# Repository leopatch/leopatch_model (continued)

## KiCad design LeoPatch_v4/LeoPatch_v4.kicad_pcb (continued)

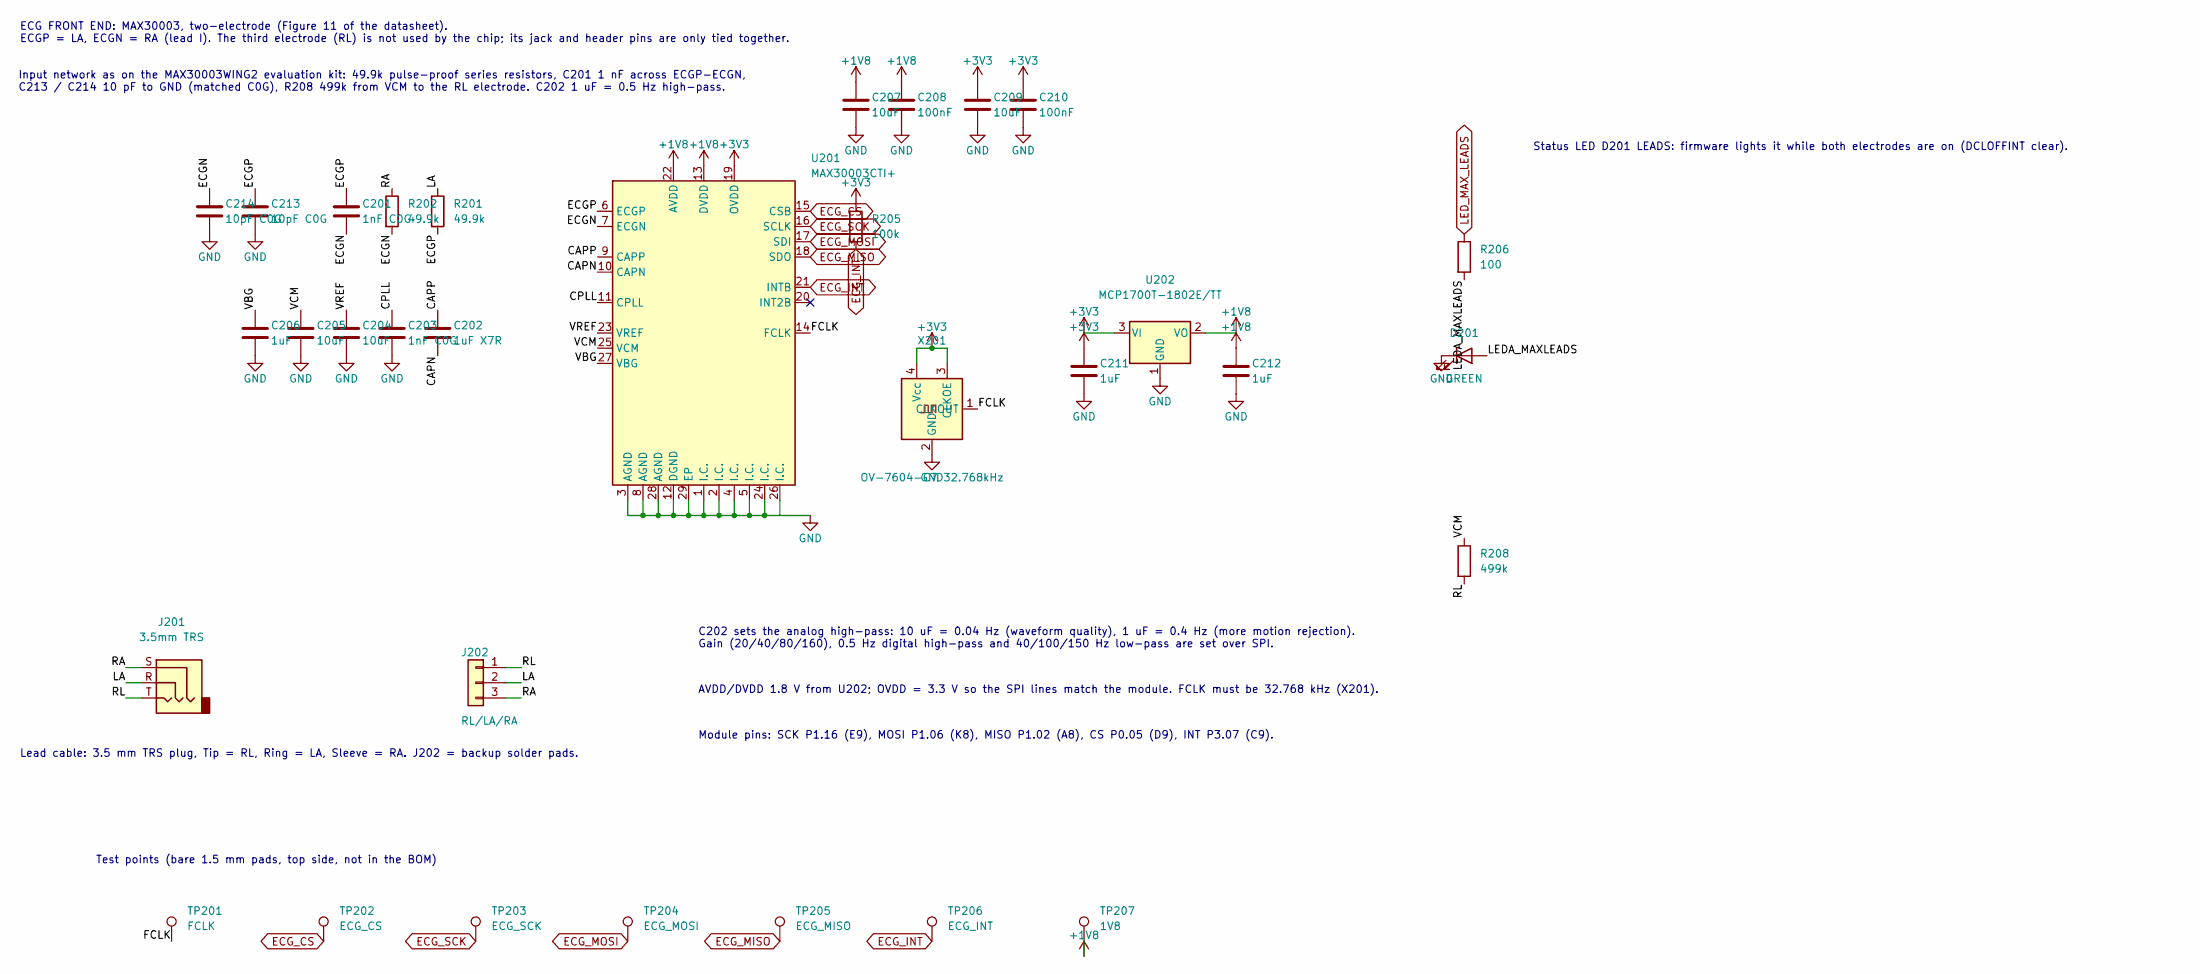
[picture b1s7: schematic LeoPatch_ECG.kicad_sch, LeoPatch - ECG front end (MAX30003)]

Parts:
C201, C203: 1nF C0G; C_0603_1608Metric; MPN CL10C102JB8NNNC; LCSC C163508
C202: 1uF X7R; C_0603_1608Metric; MPN CL10B105KP8NNNC; LCSC C95843
C204, C205, C207, C209: 10uF; C_0603_1608Metric; MPN CL10A106KP8NNNC; LCSC C19702
C206, C211, C212: 1uF; C_0603_1608Metric; MPN CL10A105KB8NNNC; LCSC C15849
C208, C210: 100nF; C_0603_1608Metric; MPN CC0603KRX7R9BB104; LCSC C14663
C213, C214: 10pF C0G; C_0603_1608Metric; MPN 0603CG100J500NT; LCSC C91367
D201: GREEN; LED_0603_1608Metric; MPN KT-0603G; LCSC C12624
J201: 3.5mm TRS; Jack_3.5mm_CUI_SJ-3523-SMT_Horizontal; MPN SJ-3523-SMT-TR; LCSC C4991872
J202: RL/LA/RA; PinHeader_1x03_P2.54mm_Vertical; MPN PZ254V-11-03P; LCSC C2937625
R201, R202: 49.9k; R_1206_3216Metric; MPN CRCW120649K9FKEAHP; LCSC C2089392
R205: 100k; R_0603_1608Metric; MPN 0603WAF1003T5E; LCSC C25803
R206: 100; R_0603_1608Metric; MPN 0603WAF1000T5E; LCSC C22775
R208: 499k; R_0603_1608Metric; MPN 0603WAF4993T5E; LCSC C26751
TP201: FCLK; TestPoint_Pad_D1.5mm
TP202: ECG_CS; TestPoint_Pad_D1.5mm
TP203: ECG_SCK; TestPoint_Pad_D1.5mm
TP204: ECG_MOSI; TestPoint_Pad_D1.5mm
TP205: ECG_MISO; TestPoint_Pad_D1.5mm
TP206: ECG_INT; TestPoint_Pad_D1.5mm
TP207: 1V8; TestPoint_Pad_D1.5mm
U201: MAX30003CTI+; TQFN-28-1EP_5x5mm_P0.5mm_EP3.25x3.25mm; MPN MAX30003CTI+T; LCSC C5354728
U202: MCP1700T-1802E/TT; SOT-23; MPN MCP1700T-1802E/TT; LCSC C150796
X201: OV-7604-C7 32.768kHz; Oscillator_SMD_SeikoEpson_SG3030CM; MPN OV-7604-C7-32.768kHz-20PPM-TA-QC; LCSC C5337982

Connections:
+1V8: C207.1, C208.1, C212.1, TP207.1, U201.13 (DVDD), U201.22 (AVDD), U202.2 (VO)
+3V3: C209.1, C210.1, C211.1, R205.1, U201.19 (OVDD), U202.3 (VI), X201.3 (CLKOE), X201.4 (Vcc); also elsewhere on the board
/ECG front end/CAPN: C202.2, U201.10 (CAPN)
/ECG front end/CAPP: C202.1, U201.9 (CAPP)
/ECG front end/CPLL: C203.1, U201.11 (CPLL)
/ECG front end/ECGN: C201.2, C214.1, R202.2, U201.7 (ECGN)
/ECG front end/ECGP: C201.1, C213.1, R201.2, U201.6 (ECGP)
/ECG front end/FCLK: TP201.1, U201.14 (FCLK), X201.1 (CLKOUT)
/ECG front end/LA: J201.R, J202.2, R201.1
/ECG front end/LEDA_MAXLEADS: D201.2 (A), R206.2
/ECG front end/RA: J201.S, J202.3, R202.1
/ECG front end/RL: J201.T, J202.1, R208.2
/ECG front end/VBG: C206.1, U201.27 (VBG)
/ECG front end/VCM: C205.1, R208.1, U201.25 (VCM)
/ECG front end/VREF: C204.1, U201.23 (VREF)
ECG_CS: TP202.1, U201.15 (CSB); also elsewhere on the board
ECG_INT: R205.2, TP206.1, U201.21 (INTB); also elsewhere on the board
ECG_MISO: TP205.1, U201.18 (SDO); also elsewhere on the board
ECG_MOSI: TP204.1, U201.17 (SDI); also elsewhere on the board
ECG_SCK: TP203.1, U201.16 (SCLK); also elsewhere on the board
GND: C203.2, C204.2, C205.2, C206.2, C207.2, C208.2, C209.2, C210.2, C211.2, C212.2, C213.2, C214.2, D201.1 (K), U201.1 (I.C.), U201.2 (I.C.), U201.3 (AGND), U201.4 (I.C.), U201.5 (I.C.), U201.8 (AGND), U201.12 (DGND), U201.24 (I.C.), U201.26 (I.C.), U201.28 (AGND), U201.29 (EP), U202.1 (GND), X201.2 (GND); also elsewhere on the board
LED_MAX_LEADS: R206.1; also elsewhere on the board

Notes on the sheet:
Lead cable: 3.5 mm TRS plug, Tip = RL, Ring = LA, Sleeve = RA. J202 = backup solder pads.
Input network as on the MAX30003WING2 evaluation kit: 49.9k pulse-proof series resistors, C201 1 nF across ECGP-ECGN, C213 / C214 10 pF to GND (matched C0G), R208 499k from VCM to the RL electrode. C202 1 uF = 0.5 Hz high-pass.
Status LED D201 LEADS: firmware lights it while both electrodes are on (DCLOFFINT clear).
ECG FRONT END: MAX30003, two-electrode (Figure 11 of the datasheet). ECGP = LA, ECGN = RA (lead I). The third electrode (RL) is not used by the chip; its jack and header pins are only tied together.
Test points (bare 1.5 mm pads, top side, not in the BOM)
Module pins: SCK P1.16 (E9), MOSI P1.06 (K8), MISO P1.02 (A8), CS P0.05 (D9), INT P3.07 (C9).
C202 sets the analog high-pass: 10 uF = 0.04 Hz (waveform quality), 1 uF = 0.4 Hz (more motion rejection). Gain (20/40/80/160), 0.5 Hz digital high-pass and 40/100/150 Hz low-pass are set over SPI.
AVDD/DVDD 1.8 V from U202; OVDD = 3.3 V so the SPI lines match the module. FCLK must be 32.768 kHz (X201).

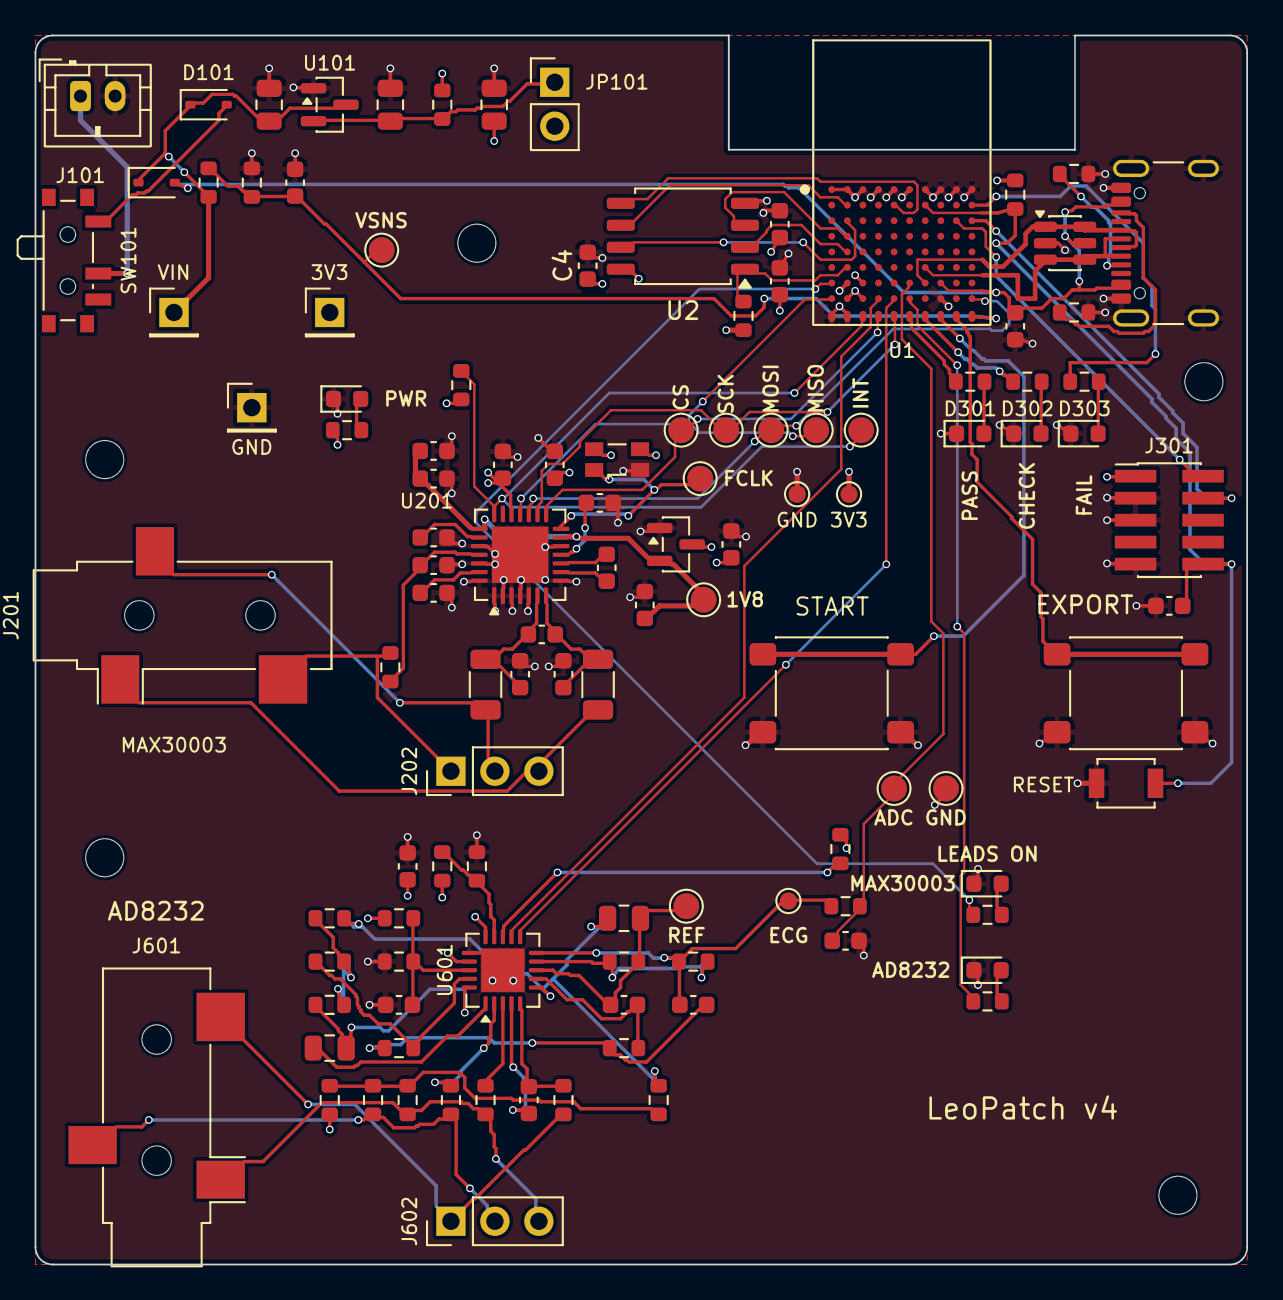
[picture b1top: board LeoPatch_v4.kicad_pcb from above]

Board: 4 copper layers, 70.0 x 71.0 mm, 118 parts (0 on the bottom side), 76 nets.

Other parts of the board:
H1, H2, H3, H4, H5: M2; MountingHole_2.2mm_M2

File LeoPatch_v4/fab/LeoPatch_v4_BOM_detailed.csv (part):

"Designator","Qty","Manufacturer","MPN","LCSC","Description","Footprint","Mount","Datasheet","Note"
"C1,C105","2","Samsung Electro-Mechanics","CL10A475KO8NNNC","C19666","4.7uF 16V X5R 10% 0603 MLCC","C_0603_1608Metric","SMD","https://www.lcsc.com/datasheet/lcsc_datasheet_2304140030_Sam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","JLC basic"
"C2,C3,C4,C104,C208,C210,C605,C607","8","YAGEO","CC0603KRX7R9BB104","C14663","100nF 50V X7R 10% 0603 MLCC","C_0603_1608Metric","SMD","https://www.lcsc.com/datasheet/lcsc_datasheet_2211101700_YAG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","JLC basic"
"C101,C102,C103","3","Samsung Electro-Mechanics","CL21A106KAYNNNE","C15850","10uF 25V X5R 10% 0805 MLCC","C_0805_2012Metric","SMD","https://www.lcsc.com/datasheet/lcsc_datasheet_2304140030_Sam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","JLC basic (C101 was 16V and C102/C103 10V in the schematic; 25V covers all three)"
"C201,C203,C601,C602","4","Samsung Electro-Mechanics","CL10C102JB8NNNC","C163508","1nF 50V C0G/NP0 5% 0603 MLCC","C_0603_1608Metric","SMD","https://www.lcsc.com/datasheet/lcsc_datasheet_2304140030_Sam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","C0G: MAX30003 ECGP-ECGN differential cap (eval kit C10 1nF), PLL, AD8232 filter"
"C202","1","Samsung Electro-Mechanics","CL10B105KP8NNNC","C95843","1uF 10V X7R 10% 0603 MLCC","C_0603_1608Metric","SMD","https://www.lcsc.com/datasheet/lcsc_datasheet_2304140030_Sam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","MAX30003 CAPP-CAPN, 0.5 Hz analog high-pass (datasheet default, eval kit C9); settles in ~1-2 s"
"C204,C205,C207,C209","4","Samsung Electro-Mechanics","CL10A106KP8NNNC","C19702","10uF 10V X5R 10% 0603 MLCC","C_0603_1608Metric","SMD","https://www.lcsc.com/datasheet/lcsc_datasheet_2304140030_Sam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","JLC basic"
"C206,C211,C212","3","Samsung Electro-Mechanics","CL10A105KB8NNNC","C15849","1uF 50V X5R 10% 0603 MLCC","C_0603_1608Metric","SMD","https://www.lcsc.com/datasheet/lcsc_datasheet_2304140030_Sam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","JLC basic"
"C603","1","FH (Guangdong Fenghua)","0603CG122J500NT","C68659","1.2nF 50V C0G/NP0 5% 0603 MLCC","C_0603_1608Metric","SMD","https://wmsc.lcsc.com/wmsc/upload/file/pdf/v2/lcsc/230414003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","AD8232 low-pass (C0G)"
"C604,C606","2","YAGEO","CC0805KKX7R9BB334","C107132","330nF 50V X7R 10% 0805 MLCC","C_0805_2012Metric","SMD","https://www.lcsc.com/datasheet/lcsc_datasheet_2304140030_YAG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","AD8232 high-pass"
"D101,D102","2","STMicroelectronics","BAT54JFILM","C86299","Schottky diode 40V 300mA SOD-323","D_SOD-323","SMD","https://www.lcsc.com/datasheet/lcsc_datasheet_2304140030_STM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","fits the SOD-323 footprint"
"D103,D201,D301,D601","4","Hubei KENTO","KT-0603G","C12624","LED green 525nm 0603","LED_0603_1608Metric","SMD","https://www.lcsc.com/datasheet/lcsc_datasheet_1806151818_Hub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","PASS, PWR, MAX30003 LEADS, AD8232 LEADS"
"D302","1","Hubei KENTO","KT-0603Y","C2287","LED yellow 590nm 0603","LED_0603_1608Metric","SMD","https://www.lcsc.com/product-detail/led-indication-discrete_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","CHECK"
"D303","1","Hubei KENTO","KT-0603R","C2286","LED red 625nm 0603","LED_0603_1608Metric","SMD","https://www.lcsc.com/datasheet/lcsc_datasheet_1810231112_Hub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","FAIL - JLC basic"
"J101","1","JST","B2B-PH-K-S(LF)(SN)","C131337","JST PH 2-pin header vertical 2.0mm, through-hole","JST_PH_B2B-PH-K_1x02_P2.00mm_Vertical","through-hole","https://www.lcsc.com/datasheet/lcsc_datasheet_2304140030_JST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","battery lead connector (mates PHR-2); through-hole"
"J102","1","Global Connector Technology","USB4105-GF-A","C3020560","USB Type-C receptacle USB 2.0 16P SMD right-angle","USB_C_Receptacle_GCT_USB4105-xx-A_16P_TopMnt_Horizontal","SMD","https://wmsc.lcsc.com/wmsc/upload/file/pdf/v2/lcsc/230414003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",""
"J103,J104,J105","3","XFCN","PZ254V-11-01P","C492400","Pin header 1x1 2.54mm vertical, through-hole","PinHeader_1x01_P2.54mm_Vertical","through-hole","https://www.lcsc.com/datasheet/lcsc_datasheet_2003141409_XFC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","alligator-clip pins; through-hole"
"J201,J601","2","CUI Devices","SJ-3523-SMT-TR","C4991872","3.5mm stereo (TRS) audio jack SMD right-angle","Jack_3.5mm_CUI_SJ-3523-SMT_Horizontal","SMD","https://wmsc.lcsc.com/wmsc/upload/file/pdf/v2/lcsc/240126111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","JLC Global Sourcing (DigiKey CP-3523SJCT-ND)"
"J202,J602","2","XFCN","PZ254V-11-03P","C2937625","Pin header 1x3 2.54mm vertical, through-hole","PinHeader_1x03_P2.54mm_Vertical","through-hole","https://wmsc.lcsc.com/wmsc/upload/file/pdf/v2/lcsc/220112180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","electrode backup header; through-hole"
"J301","1","hanxia","HX PZ1.27-2x5P TP","C41376037","Pin header 2x5 1.27mm SMD vertical (ARM SWD 10-pin)","PinHeader_2x05_P1.27mm_Vertical_SMD","SMD","https://www.lcsc.com/datasheet/lcsc_datasheet_2408301019_han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","SWD programming header"
"JP101","1","XFCN","PZ254V-11-02P","C492401","Pin header 1x2 2.54mm vertical, through-hole","PinHeader_1x02_P2.54mm_Vertical","through-hole","https://www.lcsc.com/datasheet/lcsc_datasheet_2409302300_XFC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","current-measure jumper; needs a 2.54 mm jumper cap (not assembled)"
"R1,R615","2","UNI-ROYAL","0603WAF1002T5E","C25804","10k 1% 100mW 0603 thick film","R_0603_1608Metric","SMD","https://www.lcsc.com/datasheet/lcsc_datasheet_2206010045_UNI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","JLC basic"
"R2,R205","2","UNI-ROYAL","0603WAF1003T5E","C25803","100k 1% 100mW 0603 thick film","R_0603_1608Metric","SMD","https://www.lcsc.com/datasheet/lcsc_datasheet_2206010045_UNI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","JLC basic"
"R101,R617,R619","3","UNI-ROYAL","0603WAF0000T5E","C21189","0R jumper 0603","R_0603_1608Metric","SMD","https://www.lcsc.com/datasheet/lcsc_datasheet_2411221126_UNI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","JLC basic"
"R102,R606,R607,R608,R609","5","UNI-ROYAL","0603WAF1004T5E","C22935","1M 1% 100mW 0603 thick film","R_0603_1608Metric","SMD","https://www.lcsc.com/datasheet/lcsc_datasheet_2206010130_UNI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","JLC basic"
"R103","1","UNI-ROYAL","0603WAF3303T5E","C23137","330k 1% 100mW 0603 thick film","R_0603_1608Metric","SMD","https://www.lcsc.com/datasheet/lcsc_datasheet_2206010116_UNI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","JLC basic"
"R104,R105","2","UNI-ROYAL","0603WAF5101T5E","C23186","5.1k 1% 100mW 0603 thick film","R_0603_1608Metric","SMD","https://www.lcsc.com/datasheet/lcsc_datasheet_2206010116_UNI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","USB-C CC pull-downs - JLC basic"
"R106,R302,R303,R623","4","UNI-ROYAL","0603WAF1001T5E","C21190","1k 1% 100mW 0603 thick film","R_0603_1608Metric","SMD","https://www.lcsc.com/datasheet/lcsc_datasheet_2206010130_UNI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","1k: LED resistors (yellow/red/power), AD8232 output RC (R623)"
"R201,R202","2","Vishay","CRCW120649K9FKEAHP","C2089392","49.9k 1% 750mW 1206 pulse-proof thick film","R_1206_3216Metric","SMD","https://wmsc.lcsc.com/wmsc/upload/file/pdf/v2/lcsc/230414003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","MAX30003 electrode series resistors (MAX30003WING2 eval kit: 49.9k R4/R5); pulse-proof for ESD"
"R206,R301,R621","3","UNI-ROYAL","0603WAF1000T5E","C22775","100R 1% 100mW 0603 thick film","R_0603_1608Metric","SMD","https://www.lcsc.com/datasheet/lcsc_datasheet_2411221126_UNI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","100R: green LED resistors (InGaN green needs ~3 V)"
"R601,R602,R610,R611,R613,R614","6","UNI-ROYAL","0603WAF1005T5E","C7250","10M 1% 100mW 0603 thick film","R_0603_1608Metric","SMD","https://www.lcsc.com/datasheet/lcsc_datasheet_2206010216_UNI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","JLC basic"
"R603,R604,R605","3","UNI-ROYAL","0603WAF3603T5E","C23146","360k 1% 100mW 0603 thick film","R_0603_1608Metric","SMD","https://www.lcsc.com/datasheet/lcsc_datasheet_2206010116_UNI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","AD8232 electrode + RLD safety resistors: >= 3.3 V / 10 uA = 330k (AD8232 datasheet p21, p26)"
"R612","1","UNI-ROYAL","0603WAF1404T5E","C38070","1.4M 1% 100mW 0603 thick film","R_0603_1608Metric","SMD","https://www.lcsc.com/datasheet/lcsc_datasheet_2206010000_UNI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",""
"SW101","1","C&K","PCM12SMTR","C221841","Slide switch SPDT SMD right-angle","SW_SPDT_PCM12","SMD","https://www.lcsc.com/datasheet/lcsc_datasheet_1912111437_C-K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","power on/off"
"SW301,SW302","2","C&K","PTS645SM43SMTR92 LFS","C221880","Tactile switch 6x6mm SMD 4.3mm 160gf","SW_SPST_PTS645Sx43SMTR92","SMD","https://www.lcsc.com/datasheet/lcsc_datasheet_2410121928_C-K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","EXPORT / START"
"SW303","1","Omron","B3U-1000P","C231329","Tactile switch 3x2.5mm SMD","SW_SPST_B3U-1000P","SMD","https://www.lcsc.com/product-detail/tactile-switches_omron-e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","RESET"
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
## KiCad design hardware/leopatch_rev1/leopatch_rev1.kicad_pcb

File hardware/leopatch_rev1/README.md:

# LeoPatch Rev 1 (KiCad 9)

The bare-minimum board for LeoPatch: the nRF54LM20 DK (PCA10184 v0.7.0) reduced to the parts the patch
needs, plus an AD8232 ECG front end, a LiPo battery and a 2.7 V supply. The reasoning is in
[../LeoPatch_Rev1_PCB_Plan.pdf](../LeoPatch_Rev1_PCB_Plan.pdf).

## What's on the board

| Block | Parts |
|---|---|
| Radio core (copied from the DK) | U1 nRF54LM20B, crystals X1/X2, DC/DC and decoupling, antenna tuning, test connector J1, PCB antenna |
| Power | U3 nPM1300 charger and 2.7 V supply, J10 LiPo connector, RT1 battery thermistor |
| USB-C | J3 with ESD protection D1 and choke L8 (charging and USB data) |
| Storage | U4 8 MB flash |
| User interface | LD1–LD3 green/amber/red status LEDs, SW1 record/upload button |
| Programming | P11 SWD header (connect to the DK's Debug OUT) |
| ECG | U20 AD8232 (datasheet Fig. 66), J11 electrode connector: 1 LA, 2 RA, 3 RL |
| Bring-up test points | VBAT, VSYS, VDD_NRF, ECG_OUT, GND, UART TX/RX |

Removed from the DK:
- the debugger and its USB port
- the switches and level shifters
- all pin headers
- the NFC connector
- the extra LEDs and buttons
- the reset button (the SWD header can reset the chip)
- the DK's test points

## Files

| File | What it is |
|---|---|
| `leopatch_rev1.kicad_pro` | Open this in KiCad |
| `leopatch_rev1.kicad_sch` + 5 sheets | Root sheet, plus `radio`, `power`, `usb`, `io` and `ecg` sheets |
| `leopatch_rev1.kicad_pcb` | The board, already updated to match the schematic |
| `libraries/leopatch.kicad_sym` | Symbols: nRF54LM20B, nPM1300, AD8232, MX25R6435F, USB-C, ESD, choke, RF connector, MOSFET |
| `libraries/leopatch_dk.pretty` | The DK's own footprints, copied from its board |
| `libraries/leopatch.pretty` | AD8232 LFCSP-20 (CP-20-10) and JST PH connectors |
| `reference/` | The unmodified DK board converted to KiCad, for comparison |

The libraries are registered in this folder's `sym-lib-table` and `fp-lib-table`, so the project opens
the same on any Mac with KiCad 9.

## What has been checked

- **Schematic vs. design:** every pin (412) connects to the intended net, checked against KiCad's
  exported netlist.
- **Electrical rules check:** 0 errors, 0 warnings.
- **Schematic vs. PCB** (KiCad's schematic parity check): 0 differences. Every part is on the board,
  with the right footprint, value and nets.
- **Routing:** kept parts keep the DK's routing between them. Routing that only went to removed parts
  was deleted.
- **Design rules:** set to the smallest features Nordic's layout uses. Those are 0.1 mm clearance,
  0.2 mm microvias with 0.1 mm drills, and 0.05 mm annular rings, and the DK's 8-layer filled-via
  stack-up supports them.

## Next steps in the PCB Editor

1. **Place the new parts** sitting below the board: J11 (electrodes), J10 (battery), U20 and its
   R2xx/C2xx parts, RT1, C101, R101/R102 and the test points. Put the ECG section far from the antenna
   (right edge) and from the nPM1300's inductors L6/L7.
2. **Route the 110 unrouted connections.** The ratsnest lines show them. Most are the new parts. The
   rest are connections that went through removed DK parts:
   - flash U4 straight to P2.00–P2.05
   - crystal X2 to XL1/XL2
   - nPM1300 I2C (SDA P1.12, SCL P1.13), GPIO1 and GPIO3 to the nRF54
   - USB CC1/CC2 and VBUS to the nPM1300
3. **Shrink the board outline** if you like. Keep the antenna corner, its copper-free area and the
   ground around it as they are.
4. **Leave the radio section alone:** U1 and its capacitors, X1, X2, L1, L5, FB1, FB2, C6–C8, C14,
   L2–L4, C3, C12, C13, J1, C76 and the antenna copper.
5. **Run the DRC.** Items that came with the DK file itself:
   - 3 tiny Edge.Cuts segments (they go away when you redraw the outline)
   - USB vias inside a keepout
   - the USB shield copper
   - "footprint doesn't match library" warnings, which are cosmetic

After editing the schematic, use **Tools → Update PCB from Schematic** as normal. Footprints are already
linked to their symbols.

## Design notes

- **2.7 V supply:** R17 = 330 kΩ sets the nPM1300's VOUT1 start-up voltage (250–500 kΩ = 2.7 V). The
  AD8232 needs at least 2.0 V.
- **ECG filter:** C204 = 10 nF and C205 = 1.5 nF give the datasheet's 40 Hz low-pass. 3.3 nF and
  470 pF move it to about 128 Hz, closer to the model's training data. Try both.
- **Pin map:**
  - LED0, LED1, LED2 on P1.22, P1.25, P1.27; button on P1.26
  - flash on P2.00–P2.05
  - ECG OUT on P1.03/AIN7; SDN, LO+, LO− on P1.11, P1.14, P1.15
  - PMIC SDA, SCL on P1.12, P1.13; LED power on P1.10; PMIC interrupt on P1.24. I2C clocks must use
    the chip's clock pins (datasheet table 79); P1's clock pins are P1.03, P1.04, P1.07, P1.13, P1.14,
    P1.17, P1.18, P1.23 and P1.24
  - UART TX, RX on P0.06, P0.07
- **Net names:** these are global labels, so the same name on any sheet is the same net. `#FLG` symbols are
  KiCad power flags for the rules check, not parts.

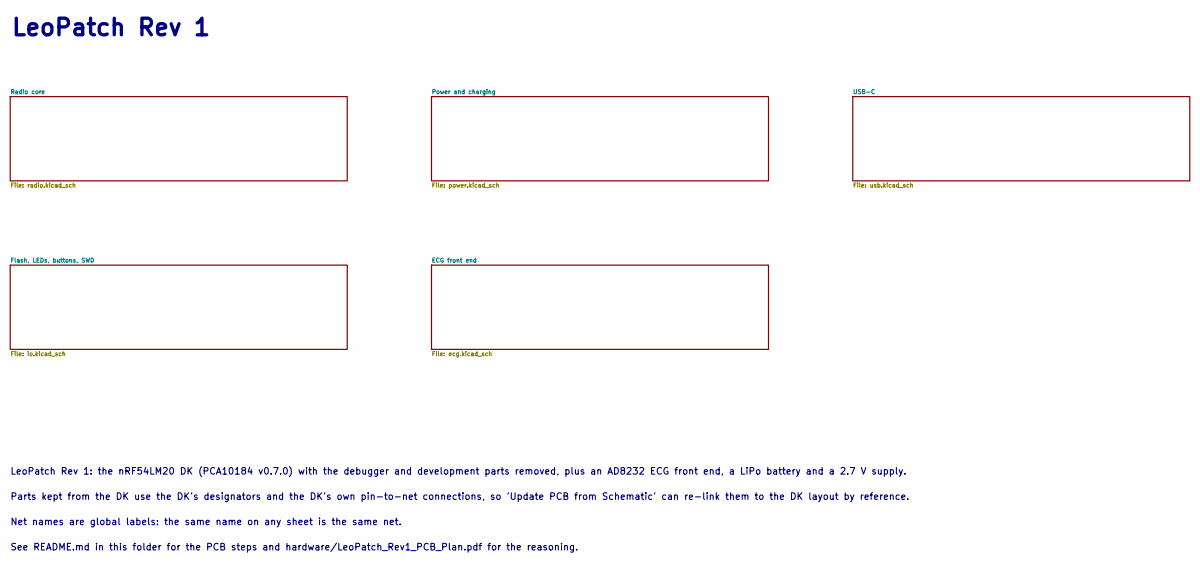
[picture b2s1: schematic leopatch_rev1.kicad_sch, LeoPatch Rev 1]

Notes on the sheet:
LeoPatch Rev 1: the nRF54LM20 DK (PCA10184 v0.7.0) with the debugger and development parts removed, plus an AD8232 ECG front end, a LiPo battery and a 2.7 V supply.
Parts kept from the DK use the DK's designators and the DK's own pin-to-net connections, so 'Update PCB from Schematic' can re-link them to the DK layout by reference.
Net names are global labels: the same name on any sheet is the same net.
See README.md in this folder for the PCB steps and hardware/LeoPatch_Rev1_PCB_Plan.pdf for the reasoning.
LeoPatch Rev 1

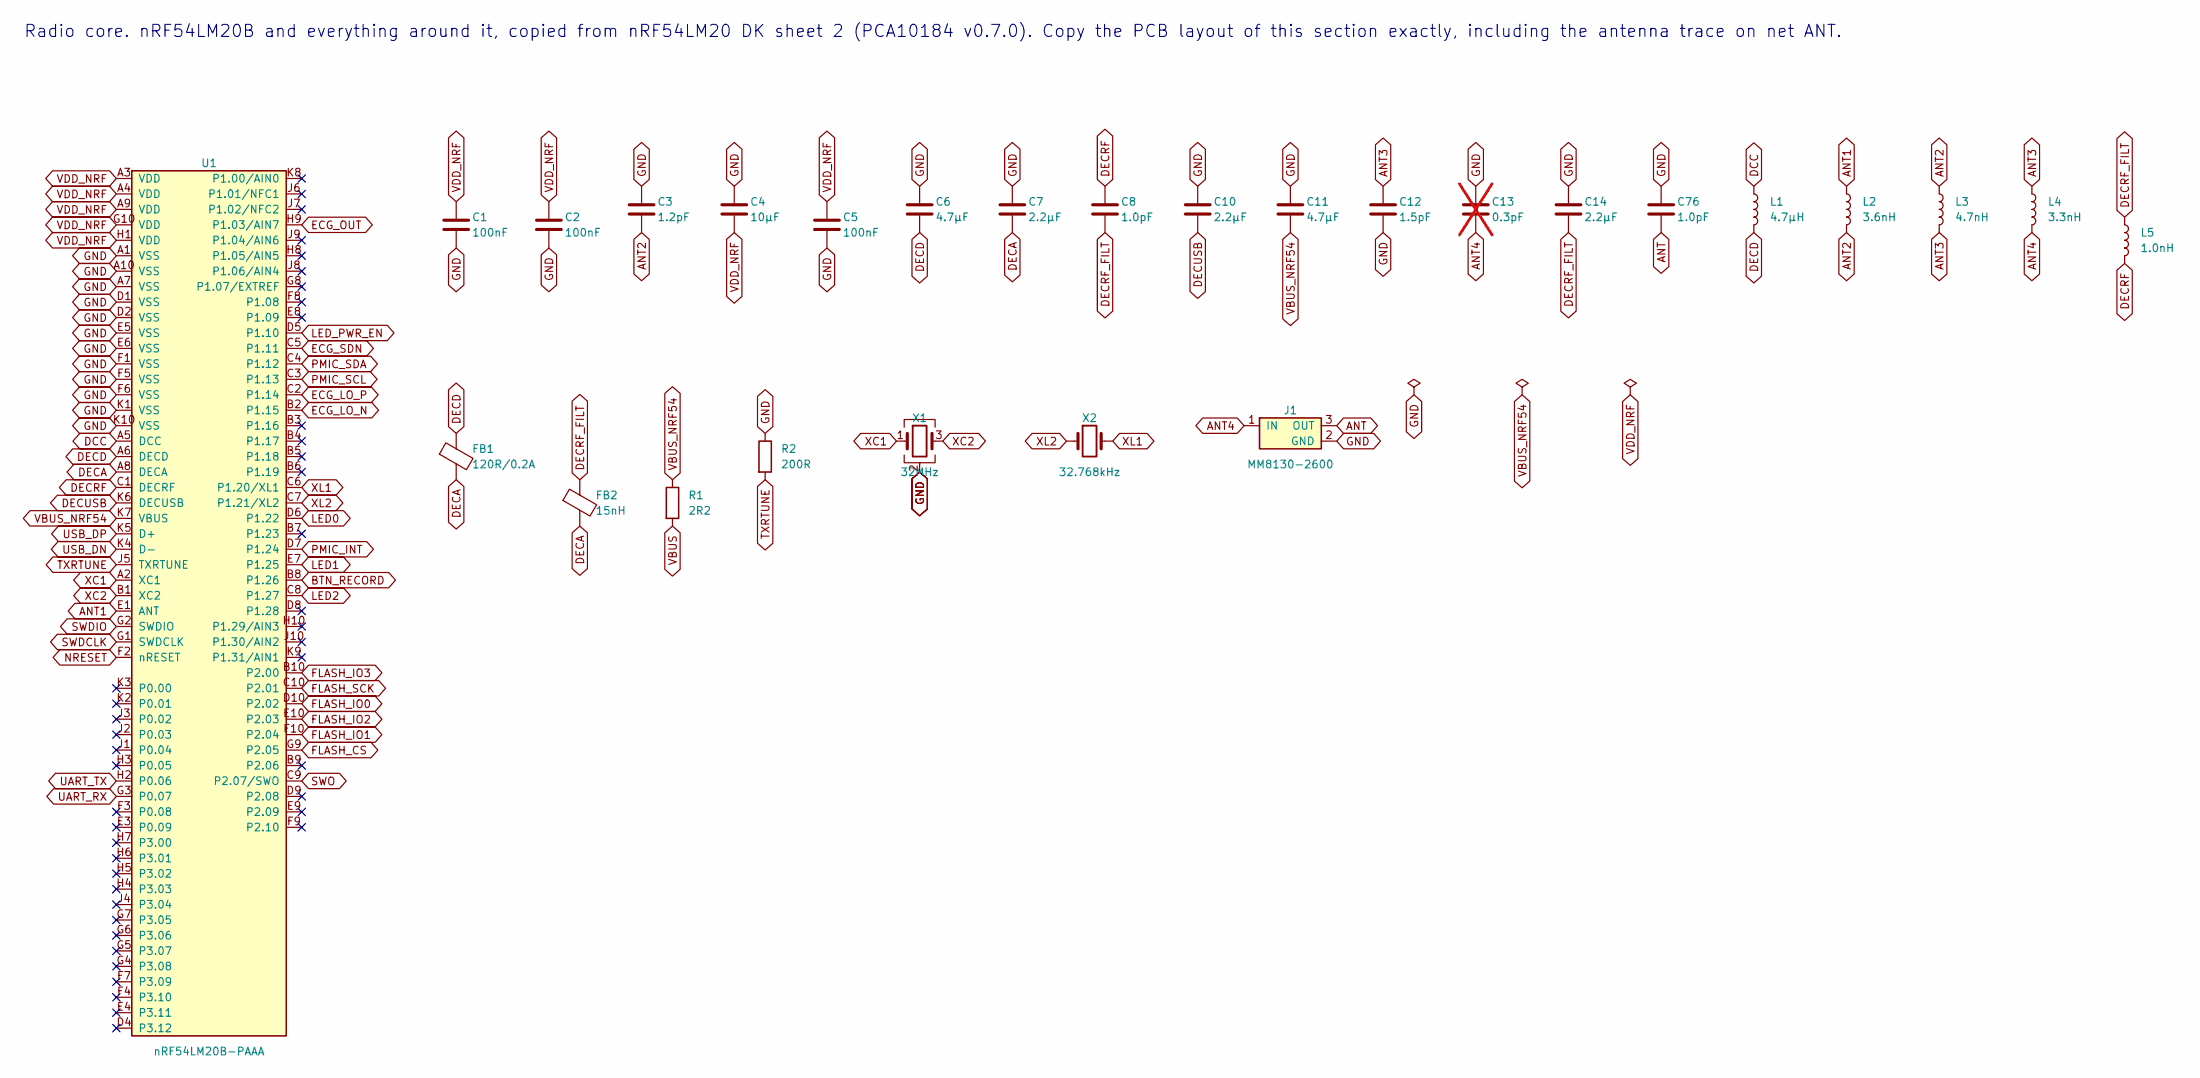
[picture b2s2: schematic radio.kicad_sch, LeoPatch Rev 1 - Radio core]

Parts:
C1, C2, C5: 100nF; CAPC0603X03L_C; MPN N.A.
C3: 1.2pF; CAPC0603X03L_C; MPN GJM0335C1H1R2WB01D
C4: 10µF; CAPC1005X04L; MPN N.A.
C6: 4.7µF; CAPC0603X03L_C; MPN GRM035R60J475ME15J
C7, C14: 2.2µF; CAPC0603X03L_C; MPN GRM033D80E225ME47D
C8: 1.0pF; CAPC0603X03L_C; MPN GJM0335C1E1R0WB01
C10: 2.2µF; CAPC0603X03L_C; MPN GRM033R61A225KE47D
C11: 4.7µF; CAPC1005X04L; MPN GRM155R61A475MEAAD
C12: 1.5pF; CAPC0603X03L_C; MPN GJM0335C1E1R5WB01
C13: 0.3pF; CAPC0603X03L_C; MPN GRM0335C1HR30BA01; not fitted
C76: 1.0pF; CAPC0603X03L_C; MPN N.A.
FB1: 120R/0.2A; INDC0603X03L_C; MPN BLM03AG121SN1D
FB2: 15nH; INDC0603X03L_C; MPN LQP03TN15NJ02D
J1: MM8130-2600; COAXIAL-SWF; MPN MM8130-2600
L1: 4.7µH; INDC1608X06L; MPN MLZ1608M4R7WT000
L2: 3.6nH; INDC0603X03L_C; MPN LQP03HQ3N6B02
L3: 4.7nH; INDC0603X03L_C; MPN LQP03HQ4N7H02
L4: 3.3nH; INDC0603X03L_C; MPN LQP03HQ3N3B02
L5: 1.0nH; INDC0603X03L_C; MPN LQP03TN1N0C02D
R1: 2R2; RESC1608X06L; MPN N.A.
R2: 200R; RESC0603X03L_C; MPN N.A.
U1: nRF54LM20B-PAAA; BGA98C35P10X10_367X385X86; MPN nRF54LM20B-PAAA-BD0
X1: 32MHz; BT-XTAL_2016; MPN CX2016DB32000D0WZRC1
X2: 32.768kHz; XTAL_2012; MPN 9HT11-32.768KDZC-T

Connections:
ANT: C76.2, J1.3 (OUT)
ANT1: L2.1, U1.E1 (ANT)
ANT2: C3.2, L2.2, L3.1
ANT3: C12.1, L3.2, L4.1
ANT4: C13.2, J1.1 (IN), L4.2
BTN_RECORD: U1.B8 (P1.26); also elsewhere on the board
DCC: L1.1, U1.A5 (DCC)
DECA: C7.2, FB1.2, FB2.2, U1.A8 (DECA)
DECD: C6.2, FB1.1, L1.2, U1.A6 (DECD)
DECRF: C8.1, L5.2, U1.C1 (DECRF)
DECRF_FILT: C8.2, C14.2, FB2.1, L5.1
DECUSB: C10.2, U1.K6 (DECUSB)
ECG_LO_N: U1.B2 (P1.15); also elsewhere on the board
ECG_LO_P: U1.C2 (P1.14); also elsewhere on the board
ECG_OUT: U1.H9 (P1.03/AIN7); also elsewhere on the board
ECG_SDN: U1.C5 (P1.11); also elsewhere on the board
FLASH_CS: U1.G9 (P2.05); also elsewhere on the board
FLASH_IO0: U1.D10 (P2.02); also elsewhere on the board
FLASH_IO1: U1.F10 (P2.04); also elsewhere on the board
FLASH_IO2: U1.E10 (P2.03); also elsewhere on the board
FLASH_IO3: U1.B10 (P2.00); also elsewhere on the board
FLASH_SCK: U1.C10 (P2.01); also elsewhere on the board
GND: C1.2, C2.2, C3.1, C4.1, C5.2, C6.1, C7.1, C10.1, C11.1, C12.2, C13.1, C14.1, C76.1, J1.2 (GND), R2.1, U1.A1 (VSS), U1.A7 (VSS), U1.A10 (VSS), U1.D1 (VSS), U1.D2 (VSS), U1.E5 (VSS), U1.E6 (VSS), U1.F1 (VSS), U1.F5 (VSS), U1.F6 (VSS), U1.K1 (VSS), U1.K10 (VSS), X1.2 (G), X1.4 (G); also elsewhere on the board
LED0: U1.D6 (P1.22); also elsewhere on the board
LED1: U1.E7 (P1.25); also elsewhere on the board
LED2: U1.C8 (P1.27); also elsewhere on the board
LED_PWR_EN: U1.D5 (P1.10); also elsewhere on the board
NRESET: U1.F2 (nRESET); also elsewhere on the board
PMIC_INT: U1.D7 (P1.24); also elsewhere on the board
PMIC_SCL: U1.C3 (P1.13); also elsewhere on the board
PMIC_SDA: U1.C4 (P1.12); also elsewhere on the board
SWDCLK: U1.G1 (SWDCLK); also elsewhere on the board
SWDIO: U1.G2 (SWDIO); also elsewhere on the board
SWO: U1.C9 (P2.07/SWO); also elsewhere on the board
TXRTUNE: R2.2, U1.J5 (TXRTUNE)
UART_RX: U1.G3 (P0.07); also elsewhere on the board
UART_TX: U1.H2 (P0.06); also elsewhere on the board
USB_DN: U1.K4 (D-); also elsewhere on the board
USB_DP: U1.K5 (D+); also elsewhere on the board
VBUS: R1.2; also elsewhere on the board
VBUS_NRF54: C11.2, R1.1, U1.K7 (VBUS)
VDD_NRF: C1.1, C2.1, C4.2, C5.1, U1.A3 (VDD), U1.A4 (VDD), U1.A9 (VDD), U1.G10 (VDD), U1.H1 (VDD); also elsewhere on the board
XC1: U1.A2 (XC1), X1.1
XC2: U1.B1 (XC2), X1.3
XL1: U1.C6 (P1.20/XL1), X2.2
XL2: U1.C7 (P1.21/XL2), X2.1

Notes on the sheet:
Radio core. nRF54LM20B and everything around it, copied from nRF54LM20 DK sheet 2 (PCA10184 v0.7.0). Copy the PCB layout of this section exactly, including the antenna trace on net ANT.

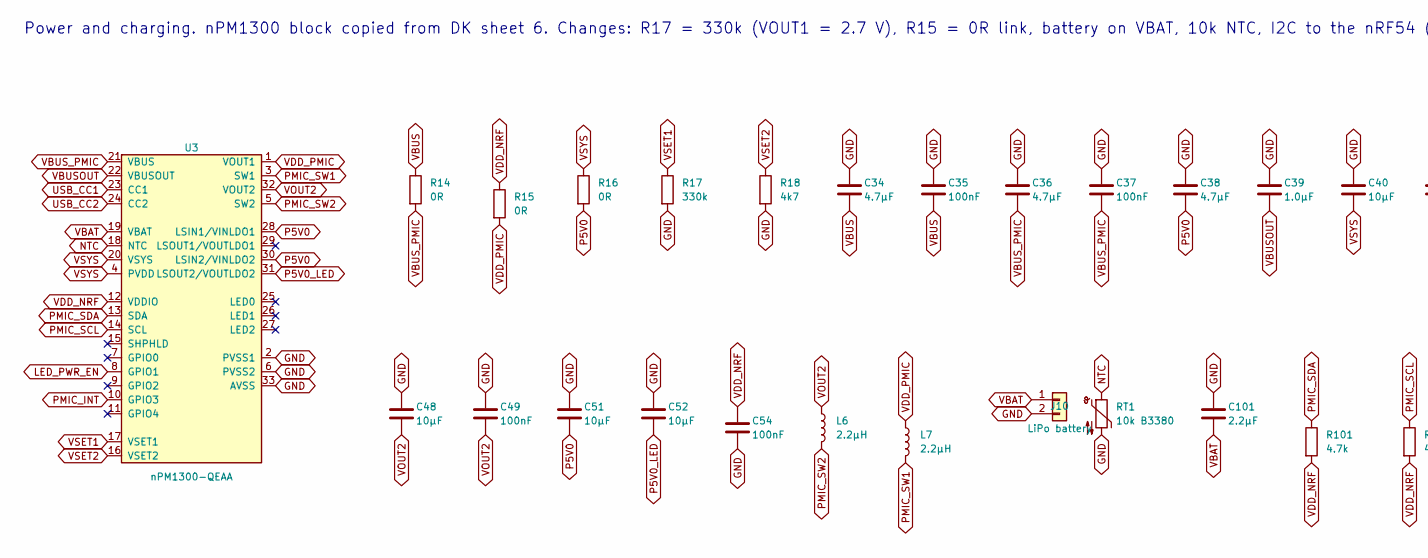
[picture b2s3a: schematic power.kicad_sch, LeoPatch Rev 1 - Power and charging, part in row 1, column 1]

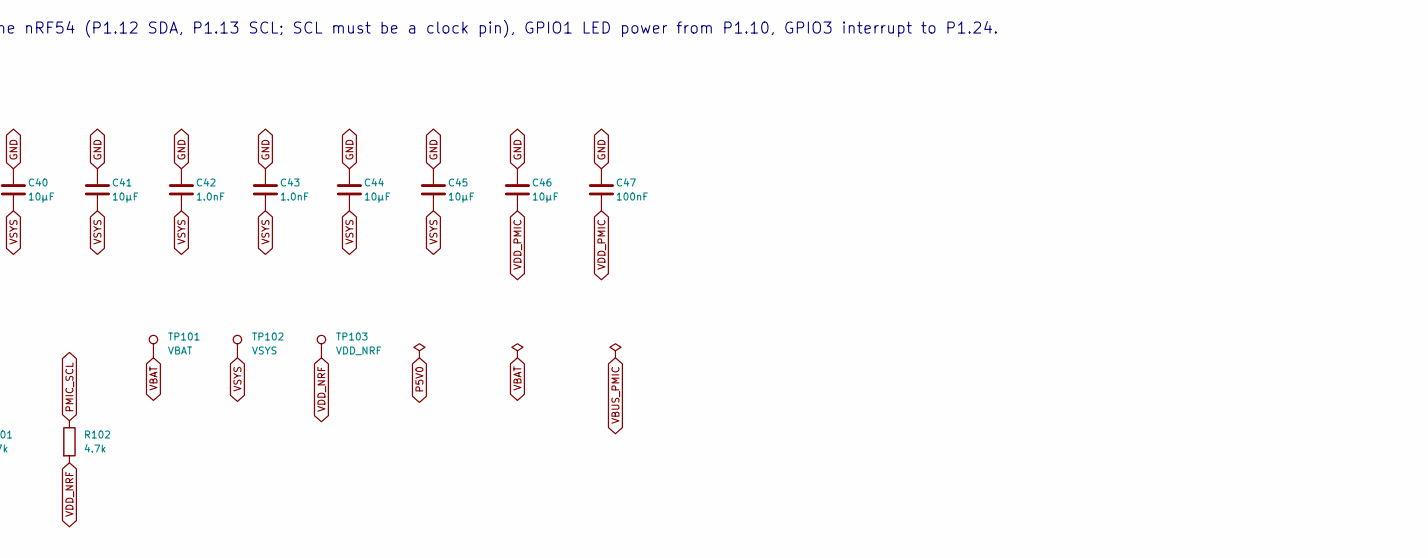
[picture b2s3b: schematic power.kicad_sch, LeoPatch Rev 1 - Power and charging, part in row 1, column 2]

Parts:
C34, C36, C38: 4.7µF; CAPC1005X04L_C2; MPN GRM155R61A475MEAA
C35, C37, C47, C49, C54: 100nF; CAPC0603X03L_C; MPN N.A.
C39: 1.0µF; CAPC1005X04L; MPN N.A.
C40, C41, C44, C45, C46, C48: 10µF; CAPC1608X06L; MPN GRM188D71A106MA73D
C42, C43: 1.0nF; CAPC0603X03L_C; MPN N.A.
C51, C52: 10µF; CAPC1608X06L; MPN N.A.
C101: 2.2µF; CAPC1005X04L
J10: LiPo battery; JST_PH_B2B-PH-K_1x02_P2.00mm_Vertical; MPN B2B-PH-K-S
L6, L7: 2.2µH; INDC2016X10N; MPN CIGT201610EH2R2MNE
R14, R15, R16: 0R; RESC1005X04L; MPN N.A.
R17: 330k; RESC0603X03L_C; MPN N.A.
R18: 4k7; RESC0603X03L_C; MPN N.A.
R101, R102: 4.7k; RESC0603X03L_C
RT1: 10k B3380; RESC1005X04L; MPN NCP15XH103F03RC
TP101: VBAT; TP_SMD_D1.5mm
TP102: VSYS; TP_SMD_D1.5mm
TP103: VDD_NRF; TP_SMD_D1.5mm
U3: nPM1300-QEAA; Nordic_QFN50P500X500X90-33N; MPN nPM1300-QEAA

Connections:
GND: C34.1, C35.1, C36.1, C37.1, C38.1, C39.1, C40.1, C41.1, C42.1, C43.1, C44.1, C45.1, C46.1, C47.1, C48.1, C49.1, C51.1, C52.1, C54.2, C101.1, J10.2, R17.2, R18.2, RT1.2, U3.2 (PVSS1), U3.6 (PVSS2), U3.33 (AVSS); also elsewhere on the board
LED_PWR_EN: U3.8 (GPIO1); also elsewhere on the board
NTC: RT1.1, U3.18 (NTC)
P5V0: C38.2, C51.2, R16.2, U3.28 (LSIN1/VINLDO1), U3.30 (LSIN2/VINLDO2)
P5V0_LED: C52.2, U3.31 (LSOUT2/VOUTLDO2); also elsewhere on the board
PMIC_INT: U3.10 (GPIO3); also elsewhere on the board
PMIC_SCL: R102.1, U3.14 (SCL); also elsewhere on the board
PMIC_SDA: R101.1, U3.13 (SDA); also elsewhere on the board
PMIC_SW1: L7.2, U3.3 (SW1)
PMIC_SW2: L6.2, U3.5 (SW2)
USB_CC1: U3.23 (CC1); also elsewhere on the board
USB_CC2: U3.24 (CC2); also elsewhere on the board
VBAT: C101.2, J10.1, TP101.1, U3.19 (VBAT)
VBUS: C34.2, C35.2, R14.1; also elsewhere on the board
VBUSOUT: C39.2, U3.22 (VBUSOUT)
VBUS_PMIC: C36.2, C37.2, R14.2, U3.21 (VBUS)
VDD_NRF: C54.1, R15.1, R101.2, R102.2, TP103.1, U3.12 (VDDIO); also elsewhere on the board
VDD_PMIC: C46.2, C47.2, L7.1, R15.2, U3.1 (VOUT1)
VOUT2: C48.2, C49.2, L6.1, U3.32 (VOUT2)
VSET1: R17.1, U3.17 (VSET1)
VSET2: R18.1, U3.16 (VSET2)
VSYS: C40.2, C41.2, C42.2, C43.2, C44.2, C45.2, R16.1, TP102.1, U3.4 (PVDD), U3.20 (VSYS)

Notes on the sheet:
Power and charging. nPM1300 block copied from DK sheet 6. Changes: R17 = 330k (VOUT1 = 2.7 V), R15 = 0R link, battery on VBAT, 10k NTC, I2C to the nRF54 (P1.12 SDA, P1.13 SCL; SCL must be a clock pin), GPIO1 LED power from P1.10, GPIO3 interrupt to P1.24.

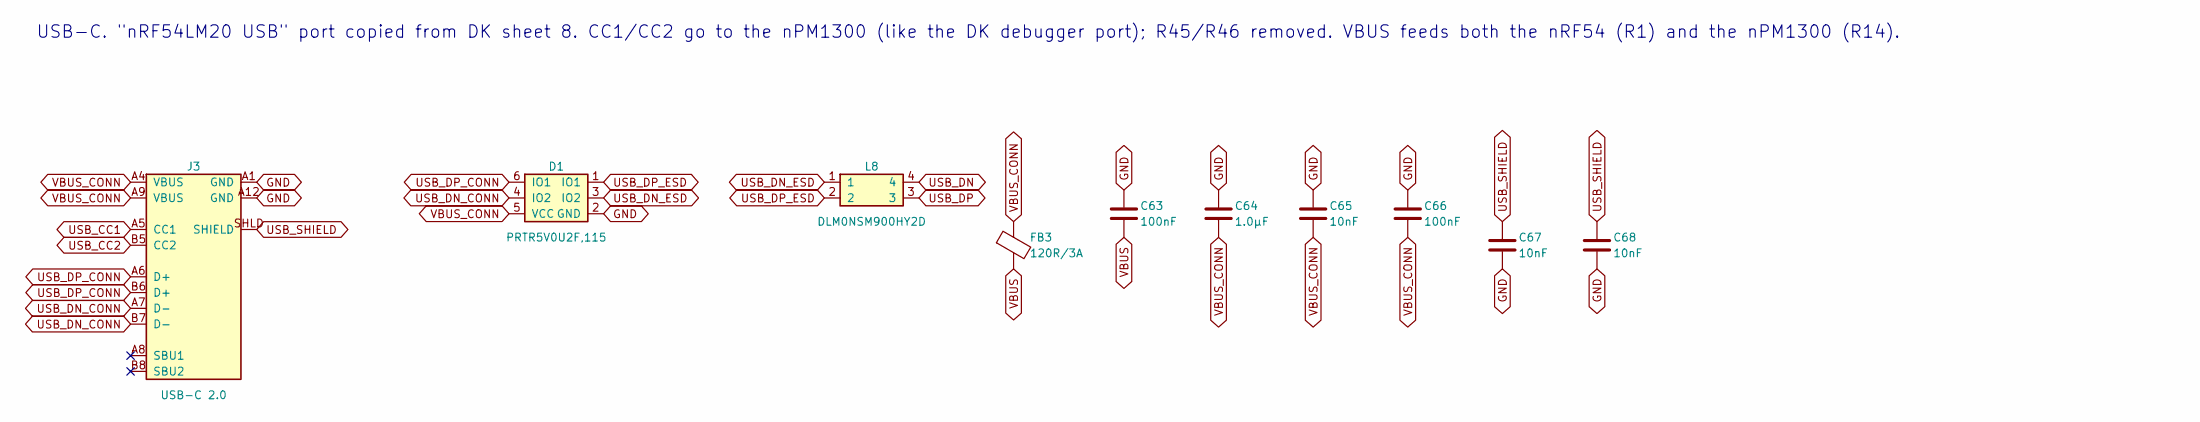
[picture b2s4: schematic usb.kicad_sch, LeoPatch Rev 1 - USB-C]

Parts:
C63, C66: 100nF; CAPC0603X03L_C; MPN N.A.
C64: 1.0µF; CAPC1005X04L; MPN GRT155R61C105KE01D
C65: 10nF; CAPC0603X03L_C; MPN N.A.
C67, C68: 10nF; CAPC1005X04L; MPN N.A.
D1: PRTR5V0U2F,115; SON50P100X50-6N; MPN PRTR5V0U2F,115
FB3: 120R/3A; INDC1608X06L; MPN BLM18KG121TN1D
J3: USB-C 2.0; SD-80259-001; MPN 80259-1021
L8: DLM0NSM900HY2D; CMC0806X05N; MPN DLM0NSM900HY2D

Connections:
GND: C63.1, C64.1, C65.1, C66.1, C67.2, C68.2, D1.2 (GND), J3.A1 (GND), J3.A12 (GND); also elsewhere on the board
USB_CC1: J3.A5 (CC1); also elsewhere on the board
USB_CC2: J3.B5 (CC2); also elsewhere on the board
USB_DN: L8.4; also elsewhere on the board
USB_DN_CONN: D1.4 (IO2), J3.A7 (D-), J3.B7 (D-)
USB_DN_ESD: D1.3 (IO2), L8.1
USB_DP: L8.3; also elsewhere on the board
USB_DP_CONN: D1.6 (IO1), J3.A6 (D+), J3.B6 (D+)
USB_DP_ESD: D1.1 (IO1), L8.2
USB_SHIELD: C67.1, C68.1, J3.SHLD (SHIELD)
VBUS: C63.2, FB3.2; also elsewhere on the board
VBUS_CONN: C64.2, C65.2, C66.2, D1.5 (VCC), FB3.1, J3.A4 (VBUS), J3.A9 (VBUS)

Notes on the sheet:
USB-C. "nRF54LM20 USB" port copied from DK sheet 8. CC1/CC2 go to the nPM1300 (like the DK debugger port); R45/R46 removed. VBUS feeds both the nRF54 (R1) and the nPM1300 (R14).
